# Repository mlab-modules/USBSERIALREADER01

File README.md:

# USBSDREADER01 - USB to SD Card Reader Module

## Overview
This module is designed to interface USB devices with SD cards, utilizing the MAX14502AETL integrated circuit. The MAX14502AETL supports both full-speed USB communication (12Mbps) for bridget devices and Hi-Speed USB communication (480Mbps) as SDcard reader, providing a versatile solution for various USB to SD card reading applications.

## Features
- **USB 2.0 Hi-Speed and Full-Speed Compliant**
- **Supports SDHC Cards**
- **Internal Hi-Speed USB SD Card Reader**
- **On-Chip Termination and Pullup Resistors**
- **Internal SD Switches for Multiplexing Two SD Cards**
- **Clock Input Frequencies: 26MHz, 19.2MHz, 13MHz, 12MHz**
- **Low-Amplitude TCXO Signal Compatibility**
- **No Power-Supply Sequencing Required**
- **1.8V to 3.3V I/O Host Microprocessor Compatibility**
- **Simple GPIO Control Mode**
- **I2C Control for Multiple Configuration Options**
- **Power-On Reset/Brown-Out Reset**

## Technical Specifications
- **Supply Voltage (VCC):** 2.4V to 3.6V
- **Logic Interface Supply Voltage (VIO):** 1.5V to 3.6V
- **USB Supply Voltage (VTM):** 2.91V to 3.4V
- **Operating Temperature Range:** -40°C to +85°C
- **Package:** 40-pin TQFN

## Pin Description
- **I2C_SEL:** I2C Select Input
- **SCL:** I2C Serial-Clock Input
- **SDA:** I2C Serial-Data I/O
- **ADD:** I2C Address Selection Input
- **BERR/INT:** Card Reader Error/Interrupt Output
- **BUSY:** Busy Output
- **MODE:** Card Reader/Pass Thru Mode Select Input
- **RST:** Reset Input
- **FREF:** Frequency Input (12MHz/13MHz/19.2MHz/26MHz)

## Schematic

## Applications
- Data loggers
- Cameras
- Flight computers

## Installation and Usage
1. **Power Supply:**
   - Connect the power supply to the VCC and GND pins.
   - Ensure the supply voltage is within the specified range (2.4V to 3.6V).

2. **USB Connection:**
   - Connect the USB data lines (D+ and D-) to the corresponding pins on the module.
   - Use the USB_B and USB_A connectors for input and output respectively.

3. **SD Card Connection:**
   - Connect the SD card signals (CMD, CLK, DAT0-3) to the corresponding pins on the module.
   - Ensure proper insertion and alignment of the SD card.

4. **I2C Configuration:**
   - If I2C control is needed, connect the I2C_SEL, SCL, and SDA pins appropriately.
   - Configure the I2C address using the ADD pin.

5. **Operation Modes:**
   - Select Pass Thru or Card Reader mode using the MODE pin.
   - Reset the device using the RST pin if necessary.

For detailed electrical characteristics and operational guidance, refer to the [MAX14502AETL Datasheet](./doc/datasheet/Maxim_Integrated-MAX14502AETL+-datasheet.pdf).

## Support
For further assistance, visit [MLAB](https://www.mlab.cz/) or contact our support team at support@mlab.cz.

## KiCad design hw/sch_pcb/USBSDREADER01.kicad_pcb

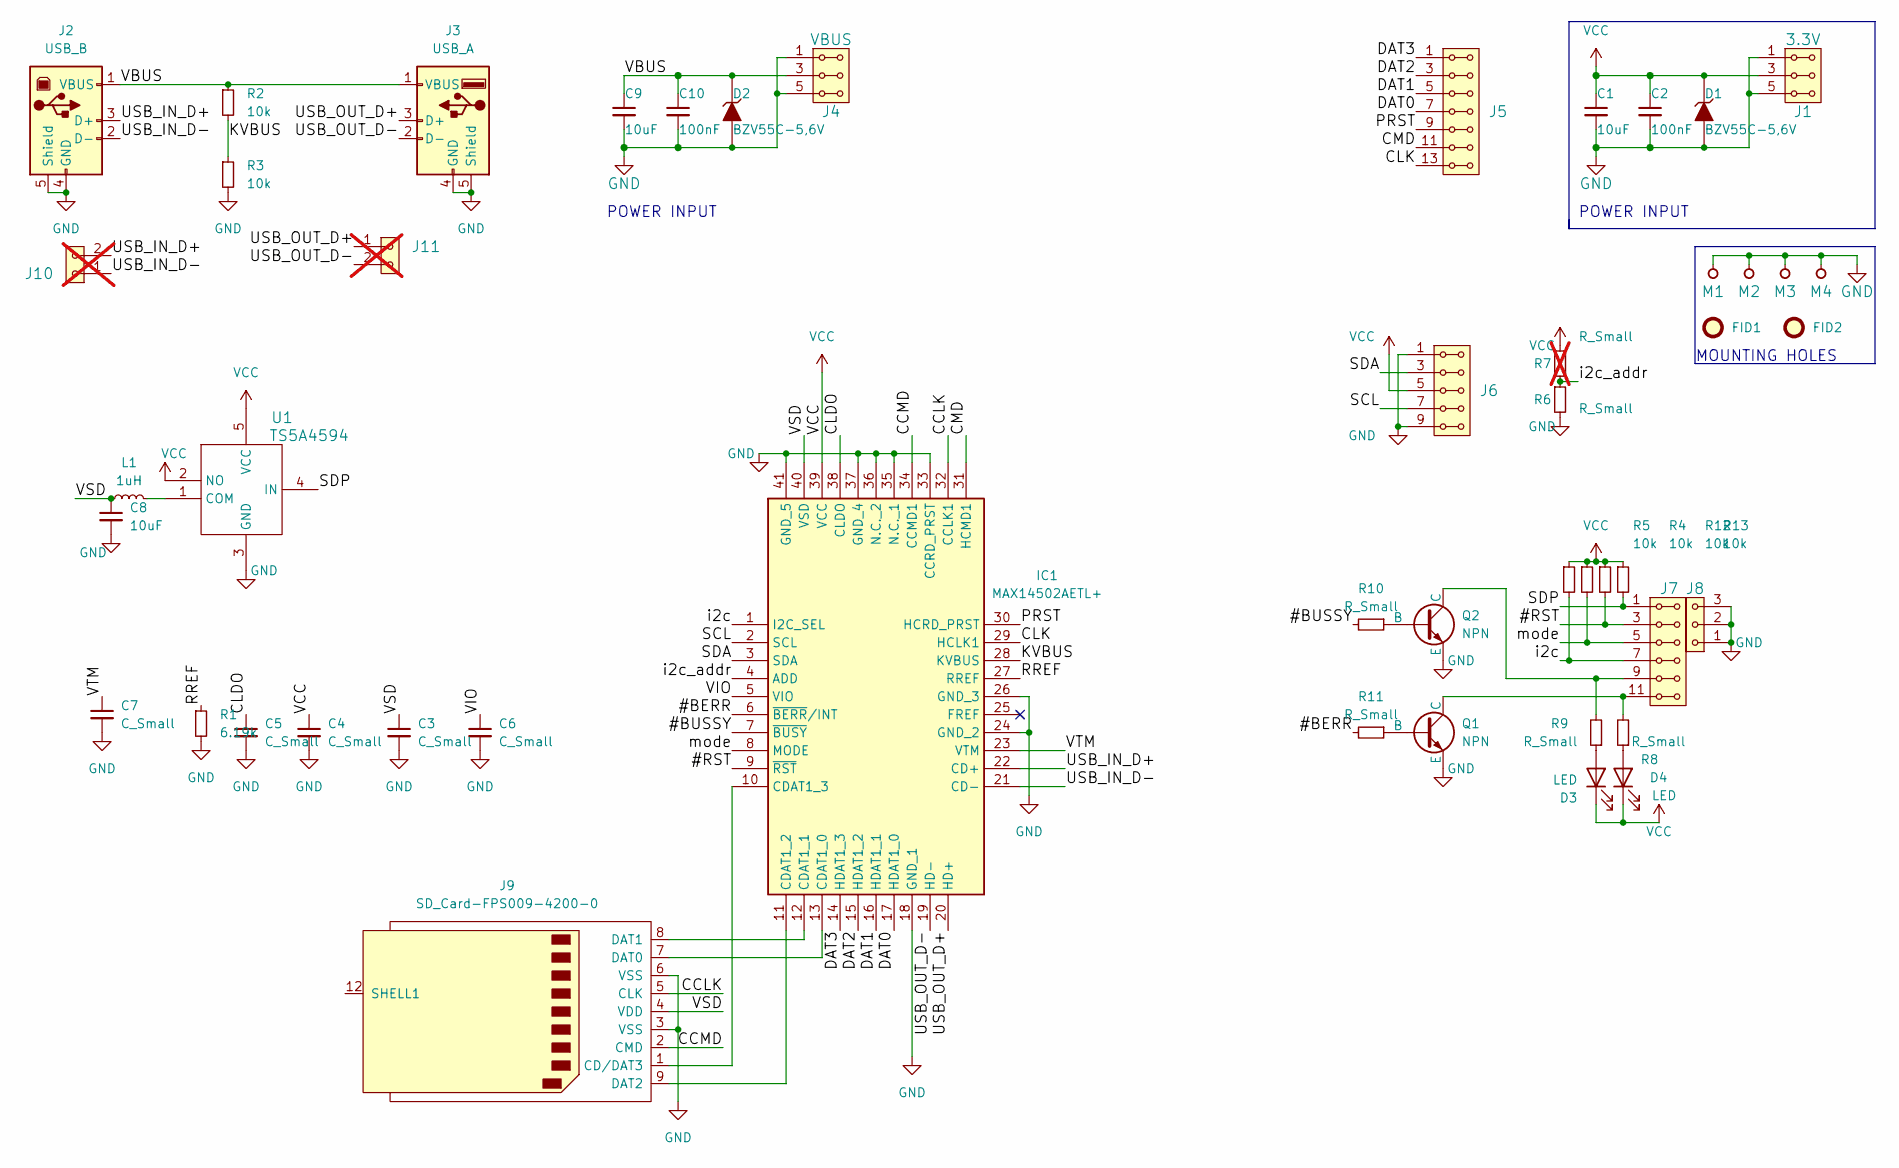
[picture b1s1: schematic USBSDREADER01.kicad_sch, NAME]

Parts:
C1, C8, C9: 10uF; C_0805_2012Metric
C2, C10: 100nF; C_0805_2012Metric
C3, C4, C5, C6, C7: C_Small; C_0805_2012Metric
D1, D2: BZV55C-5,6V; D_SMA
D3, D4: LED; LED_1206_mill
FID1, FID2: Fiducial; Fiducial_0.5mm_Mask1mm
IC1: MAX14502AETL+; QFN40P500X500X80-41N; Manufacturer_Part_Number MAX14502AETL+
J1: 3.3V; Straight_2x03
J2: USB_B; USB_B_Lumberg_2411_02_Horizontal
J3: USB_A; USB_A_CONNFLY_DS1095-WNR0
J4: VBUS; Straight_2x03
J5: HEADER_2x07_PARALLEL; PinHeader_2x07_P2.54mm_Vertical
J6: HEADER_2x05_PARALLEL; PinHeader_2x05_P2.54mm_Vertical
J7: HEADER_2x04_PARALLEL; PinHeader_2x06_P2.54mm_Vertical
J8: HEADER_1x02; PinHeader_1x03_P2.54mm_Vertical
J9: SD_Card-FPS009-4200-0; FPS009-4200-0
J10, J11: HEADER_1x02; PinHeader_1x02_P2.54mm_Vertical; not fitted
L1: 1uH; L_1008_2520Metric
M1, M2: HOLE M3; MountingHole_3mm
M3, M4: HOLE; MountingHole_3mm
Q1, Q2: NPN; SOT-23-3
R1: 6.19k; R_0805_2012Metric
R2, R3, R4, R5, R12, R13: 10k; R_0805_2012Metric
R6, R8, R9, R10, R11: R_Small; R_0805_2012Metric
R7: R_Small; R_0805_2012Metric; not fitted
U1: TS5A4594; SOT-23-5

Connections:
/#BERR: IC1.6 (~BERR/INT), R11.2
/#BUSSY: IC1.7 (~BUSY), R10.2
/#RST: IC1.9 (~RST), J7.3, J7.4, R12.2
/CCLK: IC1.32 (CCLK1), J9.5 (CLK)
/CCMD: IC1.34 (CCMD1), J9.2 (CMD)
/CLDO: C5.1, IC1.38 (CLDO)
/CLK: IC1.29 (HCLK1), J5.13, J5.14
/CMD: IC1.31 (HCMD1), J5.11, J5.12
/DAT0: IC1.17 (HDAT1_0), J5.7, J5.8
/DAT1: IC1.16 (HDAT1_1), J5.5, J5.6
/DAT2: IC1.15 (HDAT1_2), J5.3, J5.4
/DAT3: IC1.14 (HDAT1_3), J5.1, J5.2
/KVBUS: IC1.28 (KVBUS), R2.2, R3.1
/PRST: IC1.30 (HCRD_PRST), J5.9, J5.10
/RREF: IC1.27 (RREF), R1.1
/SCL: IC1.2 (SCL), J6.7, J6.8
/SDA: IC1.3 (SDA), J6.3, J6.4
/SDP: J7.1, J7.2, R13.2, U1.4 (IN)
/USB_IN_D+: IC1.22 (CD+), J2.3 (D+), J10.2
/USB_IN_D-: IC1.21 (CD-), J2.2 (D-), J10.1
/USB_OUT_D+: IC1.20 (HD+), J3.3 (D+), J11.1
/USB_OUT_D-: IC1.19 (HD-), J3.2 (D-), J11.2
/VBUS: C9.1, C10.1, D2.1 (K), J2.1 (VBUS), J3.1 (VBUS), J4.3, J4.4, R2.1
/VIO: C6.1, IC1.5 (VIO)
/VSD: C3.1, C8.1, IC1.40 (VSD), J9.4 (VDD), L1.1
/VTM: C7.1, IC1.23 (VTM)
/i2c: IC1.1 (I2C_SEL), J7.7, J7.8, R5.2
/i2c_addr: IC1.4 (ADD), R6.1, R7.2
/mode: IC1.8 (MODE), J7.5, J7.6, R4.2
GND: C1.2, C2.2, C3.2, C4.2, C5.2, C6.2, C7.2, C8.2, C9.2, C10.2, D1.2 (A), D2.2 (A), IC1.18 (GND_1), IC1.24 (GND_2), IC1.26 (GND_3), IC1.33 (CCRD_PRST), IC1.35 (N.C._1), IC1.36 (N.C._2), IC1.37 (GND_4), IC1.41 (GND_5), J1.1, J1.2, J1.5, J1.6, J2.4 (GND), J2.5 (Shield), J3.4 (GND), J3.5 (Shield), J4.1, J4.2, J4.5, J4.6, J6.1, J6.2, J6.9, J6.10, J8.1, J8.2, J8.3, J9.3 (VSS), J9.6 (VSS), M1.1, M2.1, M3.1, M4.1, Q1.3 (E), Q2.3 (E), R1.2, R3.2, R6.2, U1.3 (GND)
unnamed: D3.2 (A), R9.1
unnamed: D4.2 (A), R8.1
unnamed: IC1.13 (CDAT1_0), J9.7 (DAT0)
unnamed: IC1.12 (CDAT1_1), J9.8 (DAT1)
unnamed: IC1.11 (CDAT1_2), J9.9 (DAT2)
unnamed: IC1.10 (CDAT1_3), J9.1 (CD/DAT3)
unnamed: Q1.2 (B), R11.1
unnamed: J7.11, J7.12, Q1.1 (C), R8.2
unnamed: Q2.2 (B), R10.1
unnamed: J7.9, J7.10, Q2.1 (C), R9.2
unnamed: L1.2, U1.1 (COM)
VCC: C1.1, C2.1, C4.1, D1.1 (K), D3.1 (K), D4.1 (K), IC1.39 (VCC), J1.3, J1.4, J6.5, J6.6, R4.1, R5.1, R7.1, R12.1, R13.1, U1.2 (NO), U1.5 (VCC)

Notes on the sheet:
POWER INPUT
MOUNTING HOLES

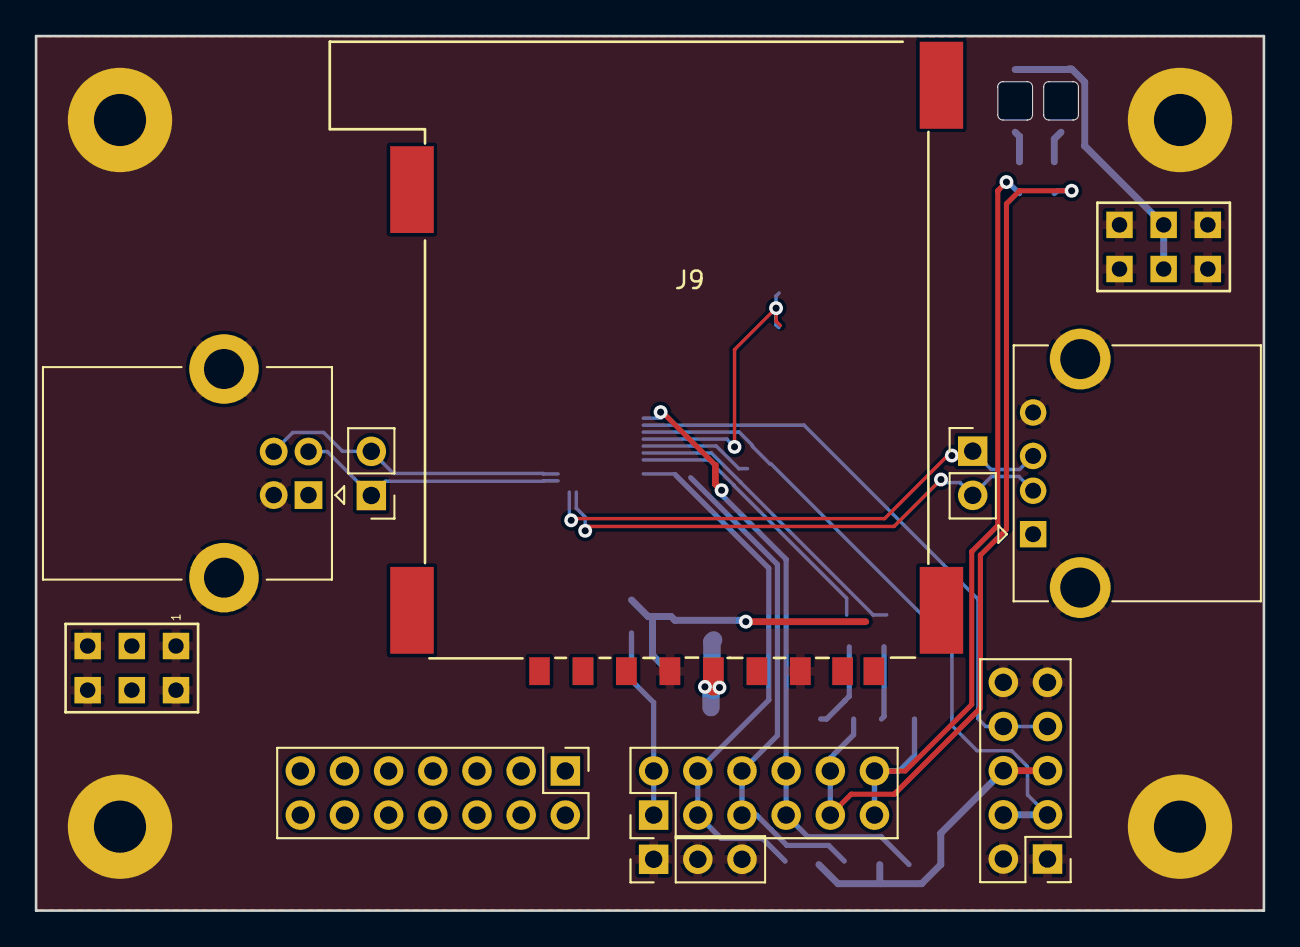
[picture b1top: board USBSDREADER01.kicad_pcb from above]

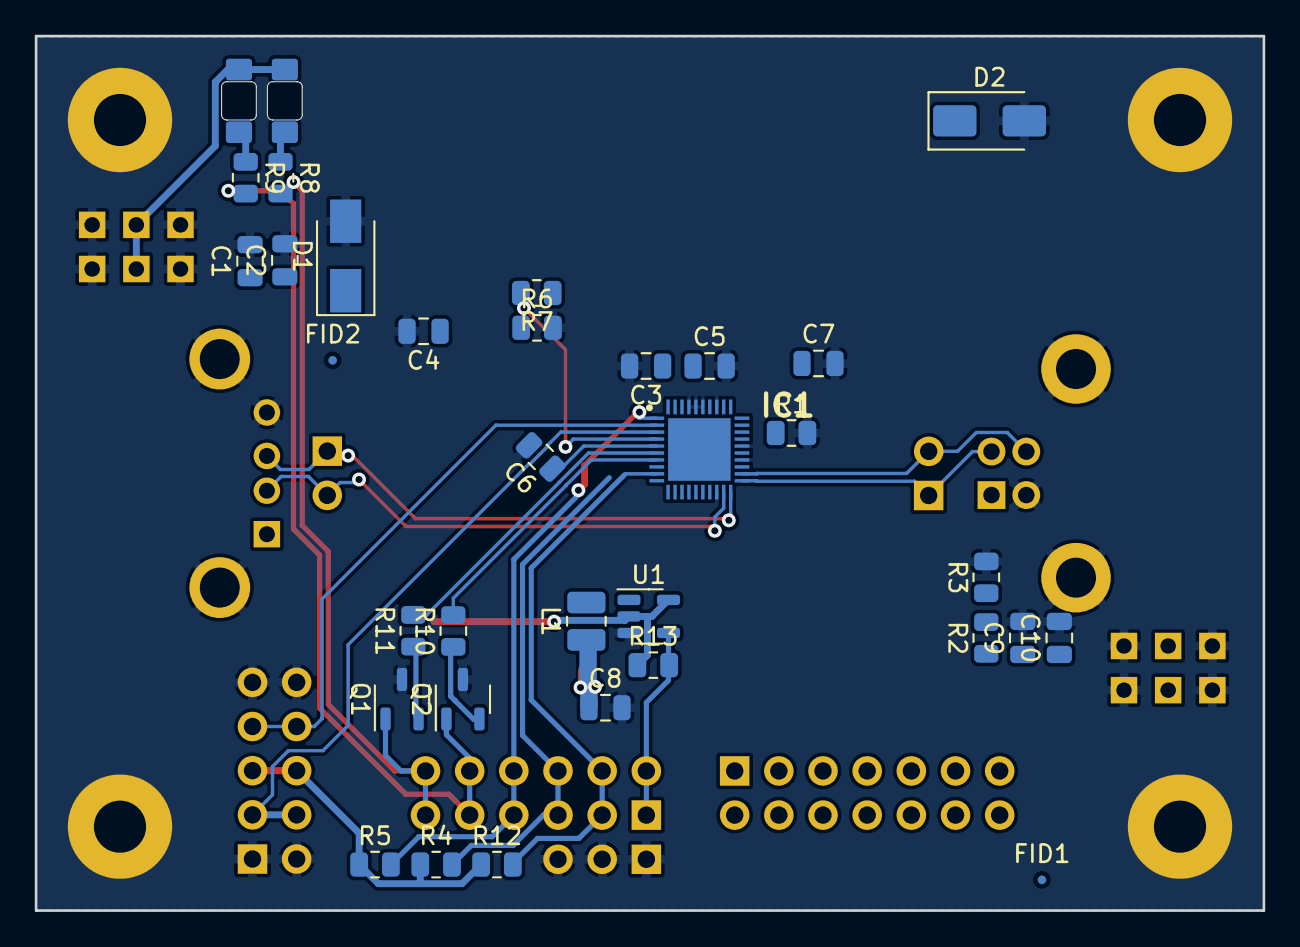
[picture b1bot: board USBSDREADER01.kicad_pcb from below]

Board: 2 copper layers, 70.6 x 50.3 mm, 49 parts (34 on the bottom side), 42 nets.

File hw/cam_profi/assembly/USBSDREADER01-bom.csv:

Component,Description,Part,References,Value,Footprint,Quantity Per PCB,Datasheet,ust_id,height,manufacturer_name,manufacturer_part_number,sim.device,sim.pins,sim.type
1,,C_Small-Device-ISM02A-rescue,C2C10,100nF,C_0805_2012Metric,2,,5c70984812875079b91f8bf2,,,,,,
2,,C_Small-Device-ISM02A-rescue,C1C9,10uF,C_0805_2012Metric,2,,5c70984812875079b91f8bbe,,,,,,
3,"Unpolarized capacitor, small symbol",C_Small,C8,10uF,C_0805_2012Metric,1,~,,,,,,,
4,"Unpolarized capacitor, small symbol",C_Small,C3C4C5C6C7,C_Small,C_0805_2012Metric,5,~,,,,,,,
5,,D_ZENER-MLAB_D,D1D2,"BZV55C-5,6V",D_SMA,2,,5c70984512875079b91f88b2,,,,,,
6,Light emitting diode,LED,D3D4,LED,LED_1206_mill,2,~,,,,,,,
7,Hi-Speed USB-to-SD Card Readers with Bypass,MAX14502AETL+,IC1,MAX14502AETL+,QFN40P500X500X80-41N,1,https://datasheet.octopart.com/MAX14502AETL%2B-Dallas-Semico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,,0.8,Analog Devices,MAX14502AETL+,,,
8,"2x03 2.54 mm pitch header, 2 pins next to each other are connected",HEADER_2x03_PARALLEL,J1,3.3V,Straight_2x03,1,,,,,,,,
9,1x03 2.54 mm pitch header,HEADER_1x03,J8,HEADER_1x02,PinHeader_1x03_P2.54mm_Vertical,1,,,,,,,,
10,"2x06 2.54 mm pitch header, 2 pins next to each other are connected",HEADER_2x06_PARALLEL,J7,HEADER_2x04_PARALLEL,PinHeader_2x06_P2.54mm_Vertical,1,,,,,,,,
11,"2x05 2.54 mm pitch header, 2 pins next to each other are connected",HEADER_2x05_PARALLEL,J6,HEADER_2x05_PARALLEL,PinHeader_2x05_P2.54mm_Vertical,1,,,,,,,,
12,"2x07 2.54 mm pitch header, 2 pins next to each other are connected",HEADER_2x07_PARALLEL,J5,HEADER_2x07_PARALLEL,PinHeader_2x07_P2.54mm_Vertical,1,,,,,,,,
13,,SD_Card-FPS009-4200-0,J9,SD_Card-FPS009-4200-0,FPS009-4200-0,1,,,,,,,,
14,USB Type A connector,USB_A,J3,USB_A,USB_A_CONNFLY_DS1095-WNR0,1, ~,,,,,,,
15,USB Type B connector,USB_B,J2,USB_B,USB_B_Lumberg_2411_02_Horizontal,1, ~,,,,,,,
16,"2x03 2.54 mm pitch header, 2 pins next to each other are connected",HEADER_2x03_PARALLEL,J4,VBUS,Straight_2x03,1,,,,,,,,
17,"Inductor, small symbol",L_Small,L1,1uH,L_1008_2520Metric,1,~,,,,,,,
18,"Bipolar transistor symbol for simulation only, substrate tied to the emitter",NPN,Q1Q2,NPN,SOT-23-3,2,~,,,,,NPN,1=C 2=B 3=E,GUMMELPOON
19,"Resistor, small symbol",R_Small,R1,6.19k,R_0805_2012Metric,1,~,,,,,,,
20,"Resistor, small symbol",R_Small,R2R3R4R5R12R13,10k,R_0805_2012Metric,6,~,,,,,,,
21,"Resistor, small symbol",R_Small,R6R8R9R10R11,R_Small,R_0805_2012Metric,5,~,,,,,,,
22,,TS5A4594,U1,TS5A4594,SOT-23-5,1,,,,,,,,

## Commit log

2023-09-27 Update metadata files
2023-09-27 Update actions products
2024-07-05 Update documentation.
2024-07-05 correct status.
